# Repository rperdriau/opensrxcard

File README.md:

# opensrxcard
opensrxcard is an open source SRX card project that consists of 
- An SRX card that can be used in all compatible Roland devices (from the XV series to the Sonic Cell)
- An Arduino Due based programmer that allows to dump, program and erase SRX cards.

This is work in progress. Keep watching.

# Further information and documentation
Please go to the [wiki for detailed documentation](https://github.com/synthtools/opensrxcard/wiki).

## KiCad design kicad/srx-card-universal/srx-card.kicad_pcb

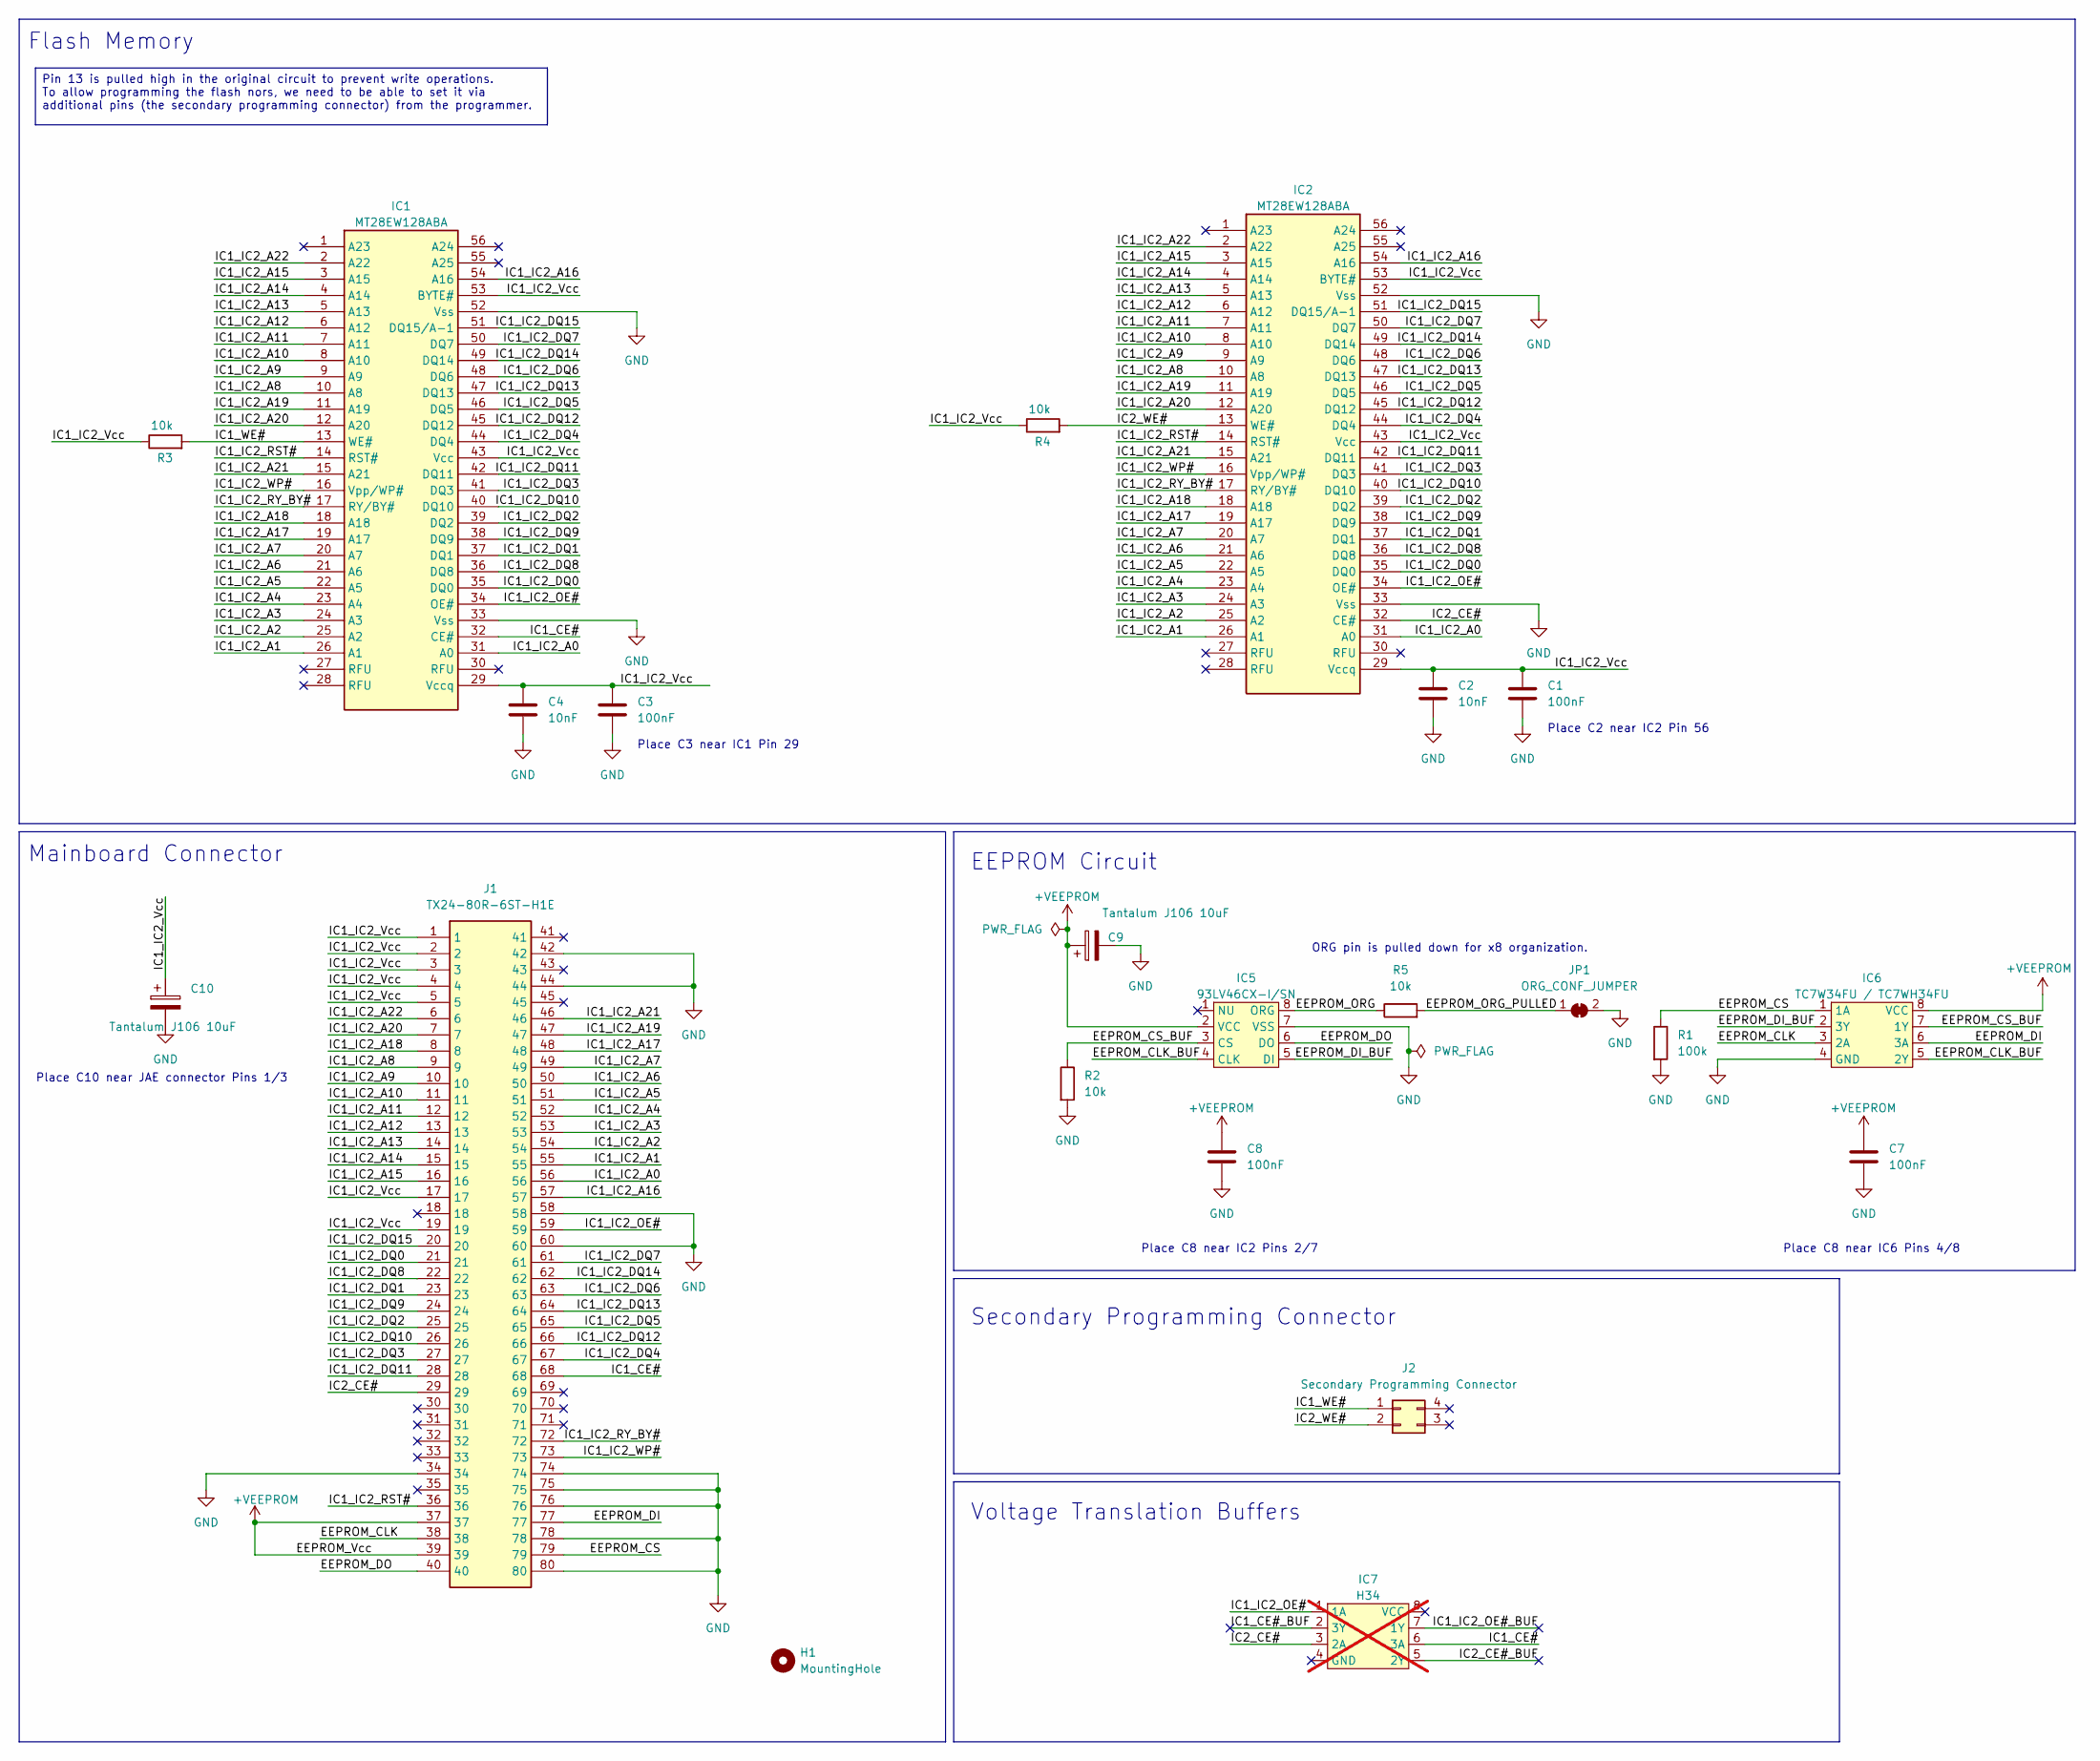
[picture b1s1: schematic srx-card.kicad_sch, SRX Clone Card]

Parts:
C1, C3, C7, C8: 100nF; C_0805_2012Metric_Pad1.18x1.45mm_HandSolder; LCSC C710699
C2, C4: 10nF; C_0805_2012Metric_Pad1.18x1.45mm_HandSolder; LCSC C161252
C9, C10: Tantalum J106 10uF; CP_EIA-3528-21_Kemet-B_Pad1.50x2.35mm_HandSolder; LCSC C110050
H1: MountingHole; MountingHole_5mm
IC1, IC2: MT28EW128ABA; TSOP-I-56_18.4x14mm_P0.5mm; LCSC C598856
IC5: 93LV46CX-I/SN; SOIC-8_3.9x4.9mm_P1.27mm
IC6: TC7W34FU / TC7WH34FU; SSOP-8_2.95x2.8mm_P0.65mm; LCSC C2676253
IC7: H34; SSOP-8_2.95x2.8mm_P0.65mm; not fitted
J1: TX24-80R-6ST-H1E; JAE_TX24-80R-6ST-H1E; Mouser Part Number 656-TX24-80R-6ST-H1E
J2: Secondary Programming Connector; PinHeader_2x02_P2.54mm_Vertical
JP1: ORG_CONF_JUMPER; SolderJumper-2_P1.3mm_Bridged_Pad1.0x1.5mm
R1: 100k; R_0805_2012Metric_Pad1.20x1.40mm_HandSolder; LCSC C122537
R2, R3, R4, R5: 10k; R_0805_2012Metric_Pad1.20x1.40mm_HandSolder; LCSC C441955

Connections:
+VEEPROM: C7.1, C8.1, C9.1, IC5.2 (VCC), IC6.8 (VCC), J1.37, J1.39
/EEPROM_CLK: IC6.3 (2A), J1.38
/EEPROM_CLK_BUF: IC5.4 (CLK), IC6.5 (2Y)
/EEPROM_CS: IC6.1 (1A), J1.79, R1.1
/EEPROM_CS_BUF: IC5.3 (CS), IC6.7 (1Y), R2.1
/EEPROM_DI: IC6.6 (3A), J1.77
/EEPROM_DI_BUF: IC5.5 (DI), IC6.2 (3Y)
/EEPROM_DO: IC5.6 (DO), J1.40
/EEPROM_ORG: IC5.8 (ORG), R5.1
/EEPROM_ORG_PULLED: JP1.1 (A), R5.2
/IC1_CE#: IC1.32 (CE#), IC7.6 (3A), J1.68
/IC1_IC2_A0: IC1.31 (A0), IC2.31 (A0), J1.56
/IC1_IC2_A1: IC1.26 (A1), IC2.26 (A1), J1.55
/IC1_IC2_A2: IC1.25 (A2), IC2.25 (A2), J1.54
/IC1_IC2_A3: IC1.24 (A3), IC2.24 (A3), J1.53
/IC1_IC2_A4: IC1.23 (A4), IC2.23 (A4), J1.52
/IC1_IC2_A5: IC1.22 (A5), IC2.22 (A5), J1.51
/IC1_IC2_A6: IC1.21 (A6), IC2.21 (A6), J1.50
/IC1_IC2_A7: IC1.20 (A7), IC2.20 (A7), J1.49
/IC1_IC2_A8: IC1.10 (A8), IC2.10 (A8), J1.9
/IC1_IC2_A9: IC1.9 (A9), IC2.9 (A9), J1.10
/IC1_IC2_A10: IC1.8 (A10), IC2.8 (A10), J1.11
/IC1_IC2_A11: IC1.7 (A11), IC2.7 (A11), J1.12
/IC1_IC2_A12: IC1.6 (A12), IC2.6 (A12), J1.13
/IC1_IC2_A13: IC1.5 (A13), IC2.5 (A13), J1.14
/IC1_IC2_A14: IC1.4 (A14), IC2.4 (A14), J1.15
/IC1_IC2_A15: IC1.3 (A15), IC2.3 (A15), J1.16
/IC1_IC2_A16: IC1.54 (A16), IC2.54 (A16), J1.57
/IC1_IC2_A17: IC1.19 (A17), IC2.19 (A17), J1.48
/IC1_IC2_A18: IC1.18 (A18), IC2.18 (A18), J1.8
/IC1_IC2_A19: IC1.11 (A19), IC2.11 (A19), J1.47
/IC1_IC2_A20: IC1.12 (A20), IC2.12 (A20), J1.7
/IC1_IC2_A21: IC1.15 (A21), IC2.15 (A21), J1.46
/IC1_IC2_A22: IC1.2 (A22), IC2.2 (A22), J1.6
/IC1_IC2_DQ0: IC1.35 (DQ0), IC2.35 (DQ0), J1.21
/IC1_IC2_DQ1: IC1.37 (DQ1), IC2.37 (DQ1), J1.23
/IC1_IC2_DQ2: IC1.39 (DQ2), IC2.39 (DQ2), J1.25
/IC1_IC2_DQ3: IC1.41 (DQ3), IC2.41 (DQ3), J1.27
/IC1_IC2_DQ4: IC1.44 (DQ4), IC2.44 (DQ4), J1.67
/IC1_IC2_DQ5: IC1.46 (DQ5), IC2.46 (DQ5), J1.65
/IC1_IC2_DQ6: IC1.48 (DQ6), IC2.48 (DQ6), J1.63
/IC1_IC2_DQ7: IC1.50 (DQ7), IC2.50 (DQ7), J1.61
/IC1_IC2_DQ8: IC1.36 (DQ8), IC2.36 (DQ8), J1.22
/IC1_IC2_DQ9: IC1.38 (DQ9), IC2.38 (DQ9), J1.24
/IC1_IC2_DQ10: IC1.40 (DQ10), IC2.40 (DQ10), J1.26
/IC1_IC2_DQ11: IC1.42 (DQ11), IC2.42 (DQ11), J1.28
/IC1_IC2_DQ12: IC1.45 (DQ12), IC2.45 (DQ12), J1.66
/IC1_IC2_DQ13: IC1.47 (DQ13), IC2.47 (DQ13), J1.64
/IC1_IC2_DQ14: IC1.49 (DQ14), IC2.49 (DQ14), J1.62
/IC1_IC2_DQ15: IC1.51 (DQ15/A-1), IC2.51 (DQ15/A-1), J1.20
/IC1_IC2_OE#: IC1.34 (OE#), IC2.34 (OE#), IC7.1 (1A), J1.59
/IC1_IC2_RST#: IC1.14 (RST#), IC2.14 (RST#), J1.36
/IC1_IC2_RY_BY#: IC1.17 (RY/BY#), IC2.17 (RY/BY#), J1.72
/IC1_IC2_Vcc: C1.1, C2.1, C3.1, C4.1, C10.1, IC1.29 (Vccq), IC1.43 (Vcc), IC1.53 (BYTE#), IC2.29 (Vccq), IC2.43 (Vcc), IC2.53 (BYTE#), J1.1, J1.2, J1.3, J1.4, J1.5, J1.17, J1.19, R3.1, R4.1
/IC1_IC2_WP#: IC1.16 (Vpp/WP#), IC2.16 (Vpp/WP#), J1.73
/IC1_WE#: IC1.13 (WE#), J2.1, R3.2
/IC2_CE#: IC2.32 (CE#), IC7.3 (2A), J1.29
/IC2_WE#: IC2.13 (WE#), J2.2, R4.2
GND: C1.2, C2.2, C3.2, C4.2, C7.2, C8.2, C9.2, C10.2, IC1.33 (Vss), IC1.52 (Vss), IC2.33 (Vss), IC2.52 (Vss), IC5.7 (VSS), IC6.4 (GND), J1.34, J1.42, J1.44, J1.58, J1.60, J1.74, J1.75, J1.76, J1.78, J1.80, JP1.2 (B), R1.2, R2.2

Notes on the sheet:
Flash Memory
Place C3 near IC1 Pin 29
Place C10 near JAE connector Pins 1/3
Place C2 near IC2 Pin 56
ORG pin is pulled down for x8 organization.
Voltage Translation Buffers
EEPROM Circuit
Place C8 near IC6 Pins 4/8
Place C8 near IC2 Pins 2/7
Secondary Programming Connector
Mainboard Connector
Pin 13 is pulled high in the original circuit to prevent write operations. To allow programming the flash nors, we need to be able to set it via additional pins (the secondary programming connector) from the programmer.

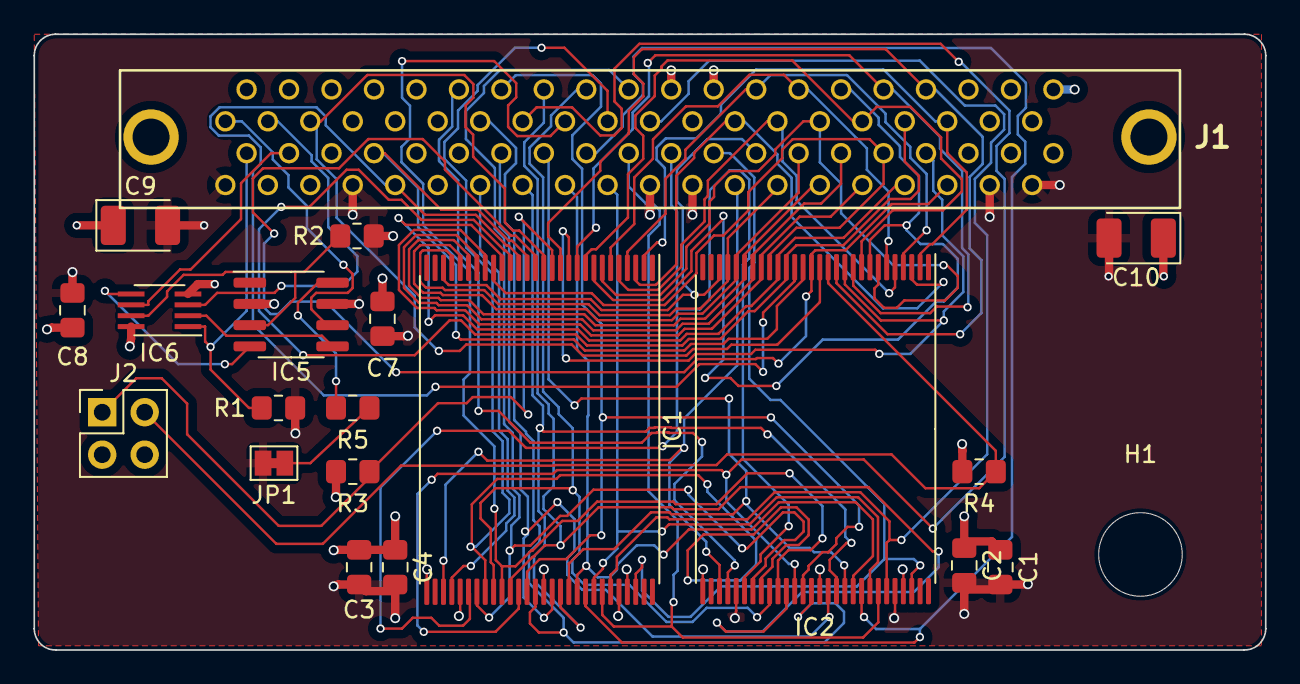
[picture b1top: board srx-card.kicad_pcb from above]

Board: 4 copper layers, 73.7 x 36.8 mm, 21 parts (0 on the bottom side), 59 nets.

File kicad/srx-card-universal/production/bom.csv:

Designator,Footprint,Quantity,Value,LCSC Part #
"C1, C3, C7, C8",0805,4,100nF,C49678
C10,CP_EIA-3528-21_Kemet-B_Pad1.50x2.35mm_HandSolder,1,Tantalum J106 10uF,C123255
"C2, C4",0805,2,10nF,C1710
C9,CP_EIA-3528-21_Kemet-B_Pad1.50x2.35mm_HandSolder,1,Tantalum J106 10uF,C123255
"IC1, IC2",TSOP-I-56_18.4x14mm_P0.5mm,2,MT28EW128ABA,C598856
R1,0805,1,100k,C149504
"R2, R3, R4, R5",0805,4,10k,C17414

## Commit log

2024-04-11 add license.
2025-12-21 Update README to clarify SRX card compatibility
2025-12-22 Reformat BOM CSV for consistency
2026-01-02 Upload separate files for SMD and SMD+TH versions
    Add a SMD + through-hole version for the people who would like to order assembled PCBs with connectors. Rename the SMD-only initial version. Modify the orientation of Flash EPROMs for better verifica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
